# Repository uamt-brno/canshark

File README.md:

canshark
========

Wireshark sniffer for CAN bus

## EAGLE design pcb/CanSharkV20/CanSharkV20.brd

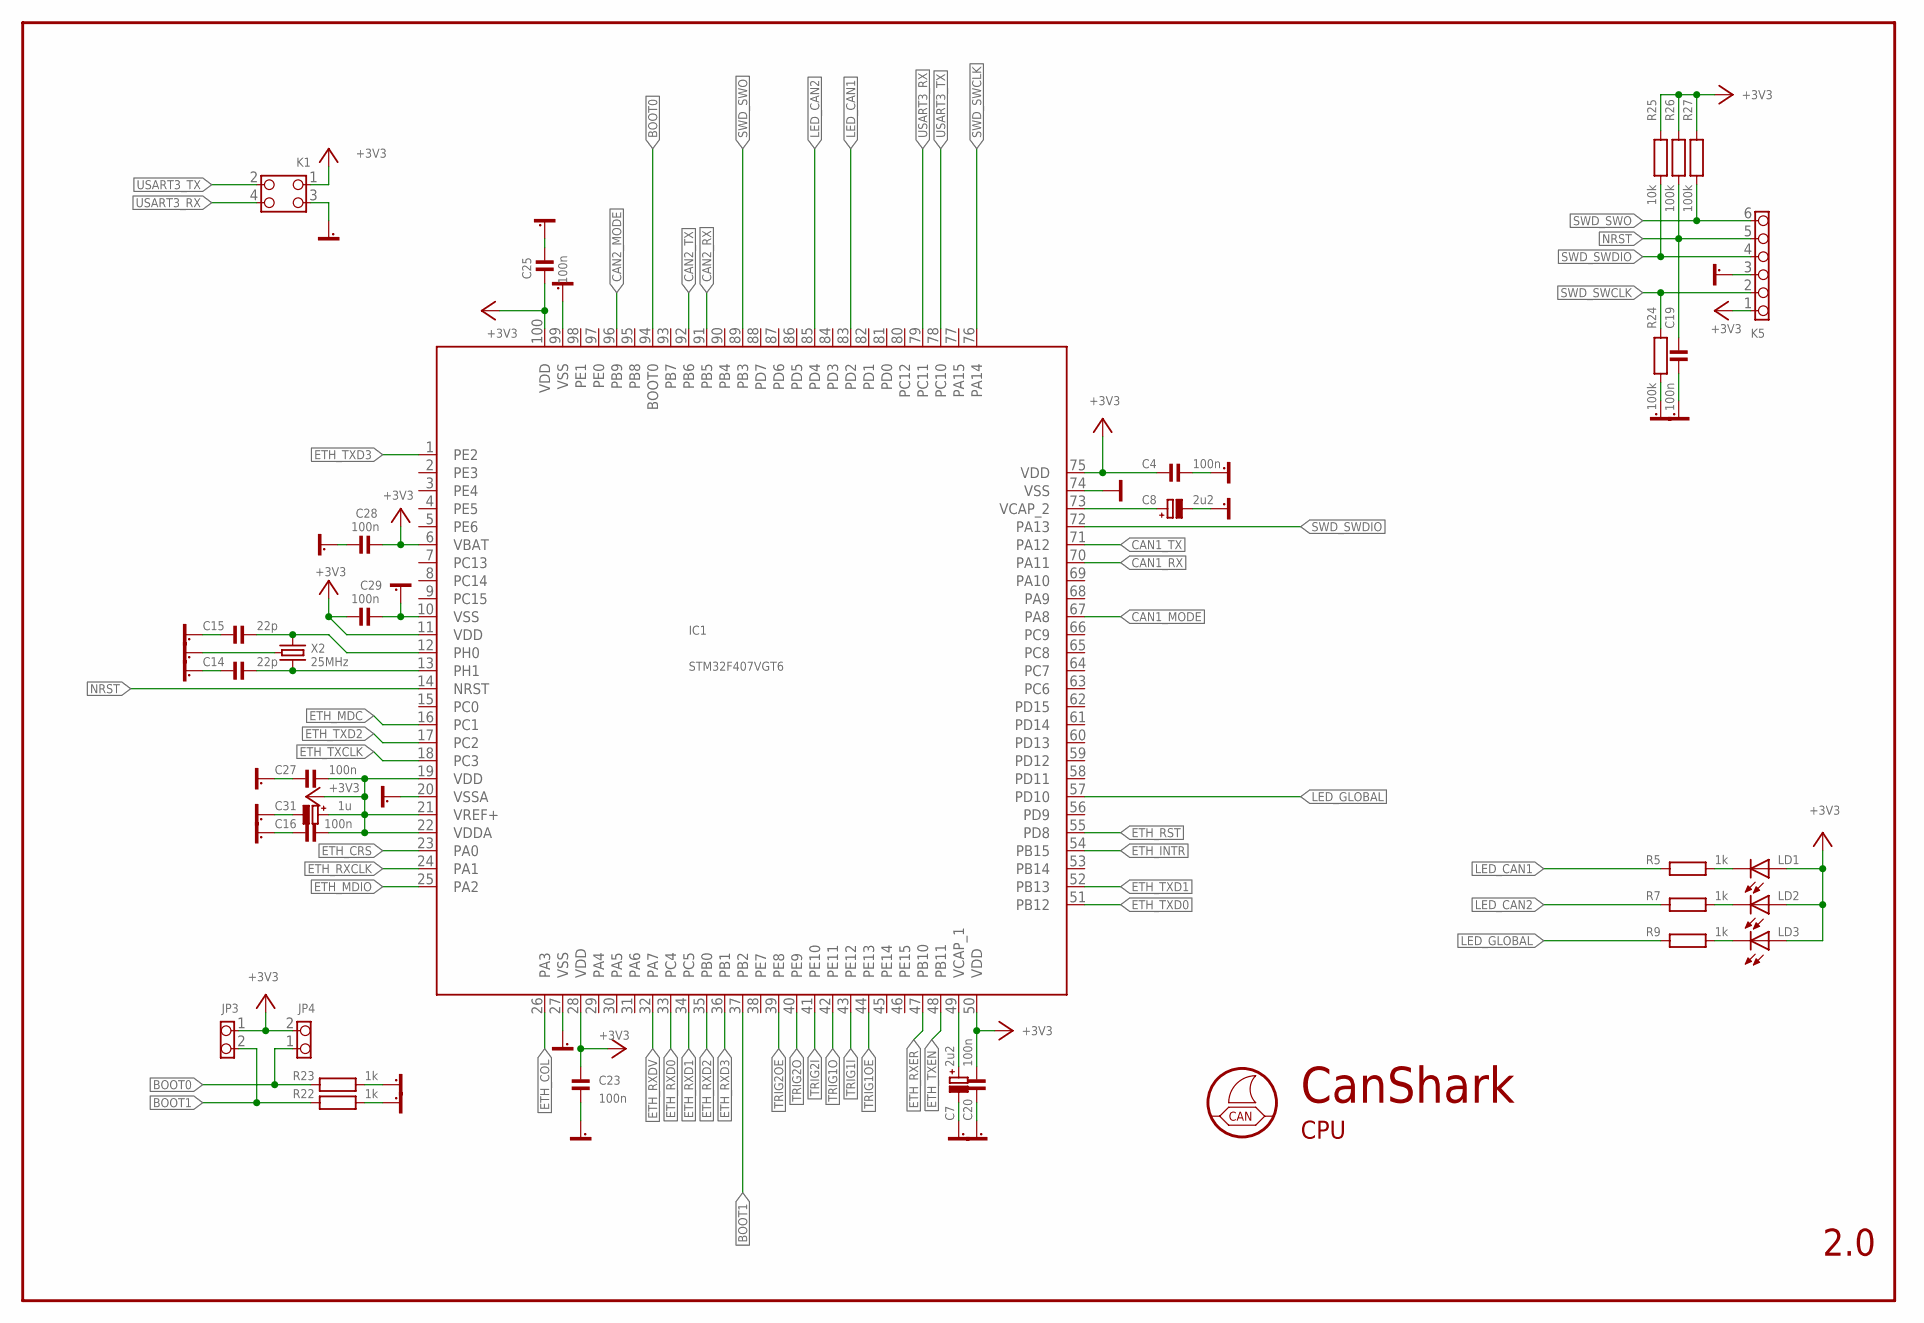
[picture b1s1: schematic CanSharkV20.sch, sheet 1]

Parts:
C4, C16, C19, C20, C23, C25, C27, C28, C29: 100n; 0603
C7, C8: 2u2; CT3216A
C14, C15: 22p; 0603
C31: 1u; CT3216A
IC1: STM32F407VGT6; LQFP100
JP3, JP4: PINHD-1X2; 1X02_254
K1: PINHD-2X2; 2X02_254
K5: PINHD-1X6; 1X06_254
LD1, LD2, LD3: TLLG4400; LED3MM
R5, R7, R9, R22, R23: 1k; 0603
R24, R25, R27: 100k; 0603
R26: 10k; 0603
X2: 25MHz; X_XT324

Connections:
+3V3: C4.2, C16.1, C20.1, C23.1, C25.2, C27.1, C28.2, C29.2, C31.+, IC1.6 (VBAT), IC1.11 (VDD), IC1.19 (VDD), IC1.21 (VREF+), IC1.22 (VDDA), IC1.28 (VDD), IC1.50 (VDD), IC1.75 (VDD), IC1.100 (VDD), JP3.1, JP4.2, K1.1, K5.1, LD1.A, LD2.A, LD3.A, R25.1, R26.2, R27.1; also elsewhere on the board
BOOT0: IC1.94 (BOOT0), JP4.1, R23.2
BOOT1: IC1.37 (PB2), JP3.2, R22.2
CAN1_MODE: IC1.67 (PA8); also elsewhere on the board
CAN1_RX: IC1.70 (PA11); also elsewhere on the board
CAN1_TX: IC1.71 (PA12); also elsewhere on the board
CAN2_MODE: IC1.96 (PB9); also elsewhere on the board
CAN2_RX: IC1.91 (PB5); also elsewhere on the board
CAN2_TX: IC1.92 (PB6); also elsewhere on the board
ETH_COL: IC1.26 (PA3); also elsewhere on the board
ETH_CRS: IC1.23 (PA0); also elsewhere on the board
ETH_INTR: IC1.54 (PB15); also elsewhere on the board
ETH_MDC: IC1.16 (PC1); also elsewhere on the board
ETH_MDIO: IC1.25 (PA2); also elsewhere on the board
ETH_RST: IC1.55 (PD8); also elsewhere on the board
ETH_RXCLK: IC1.24 (PA1); also elsewhere on the board
ETH_RXD0: IC1.33 (PC4); also elsewhere on the board
ETH_RXD1: IC1.34 (PC5); also elsewhere on the board
ETH_RXD2: IC1.35 (PB0); also elsewhere on the board
ETH_RXD3: IC1.36 (PB1); also elsewhere on the board
ETH_RXDV: IC1.32 (PA7); also elsewhere on the board
ETH_RXER: IC1.47 (PB10); also elsewhere on the board
ETH_TXCLK: IC1.18 (PC3); also elsewhere on the board
ETH_TXD0: IC1.51 (PB12); also elsewhere on the board
ETH_TXD1: IC1.52 (PB13); also elsewhere on the board
ETH_TXD2: IC1.17 (PC2); also elsewhere on the board
ETH_TXD3: IC1.1 (PE2); also elsewhere on the board
ETH_TXEN: IC1.48 (PB11); also elsewhere on the board
GND: IC1.74 (VSS)
GND1: C4.1, C7.-, C8.-, C14.2, C15.2, C16.2, C19.2, C20.2, C23.2, C25.1, C27.2, C28.1, C29.1, C31.-, IC1.10 (VSS), IC1.20 (VSSA), IC1.27 (VSS), IC1.99 (VSS), K1.3, K5.3, R22.1, R23.1, R24.2, X2.2 (G), X2.4 (G); also elsewhere on the board
LED_CAN1: IC1.83 (PD2), R5.2
LED_CAN2: IC1.85 (PD4), R7.2
LED_GLOBAL: IC1.57 (PD10), R9.2
unnamed: C7.+, IC1.49 (VCAP_1)
unnamed: C8.+, IC1.73 (VCAP_2)
unnamed: LD1.K (C), R5.1
unnamed: LD2.K (C), R7.1
unnamed: LD3.K (C), R9.1
NRST: C19.1, IC1.14 (NRST), K5.5, R26.1
OSC_IN: C15.1, IC1.12 (PH0), X2.1
OSC_OUT: C14.1, IC1.13 (PH1), X2.3 (2)
SWD_SWCLK: IC1.76 (PA14), K5.2, R24.1
SWD_SWDIO: IC1.72 (PA13), K5.4, R25.2
SWD_SWO: IC1.89 (PB3), K5.6, R27.2
TRIG1I: IC1.43 (PE12); also elsewhere on the board
TRIG1O: IC1.42 (PE11); also elsewhere on the board
TRIG1OE: IC1.44 (PE13); also elsewhere on the board
TRIG2I: IC1.41 (PE10); also elsewhere on the board
TRIG2O: IC1.40 (PE9); also elsewhere on the board
TRIG2OE: IC1.39 (PE8); also elsewhere on the board
USART3_RX: IC1.79 (PC11), K1.4
USART3_TX: IC1.78 (PC10), K1.2

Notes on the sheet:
CAN
2.0
CanShark
CPU

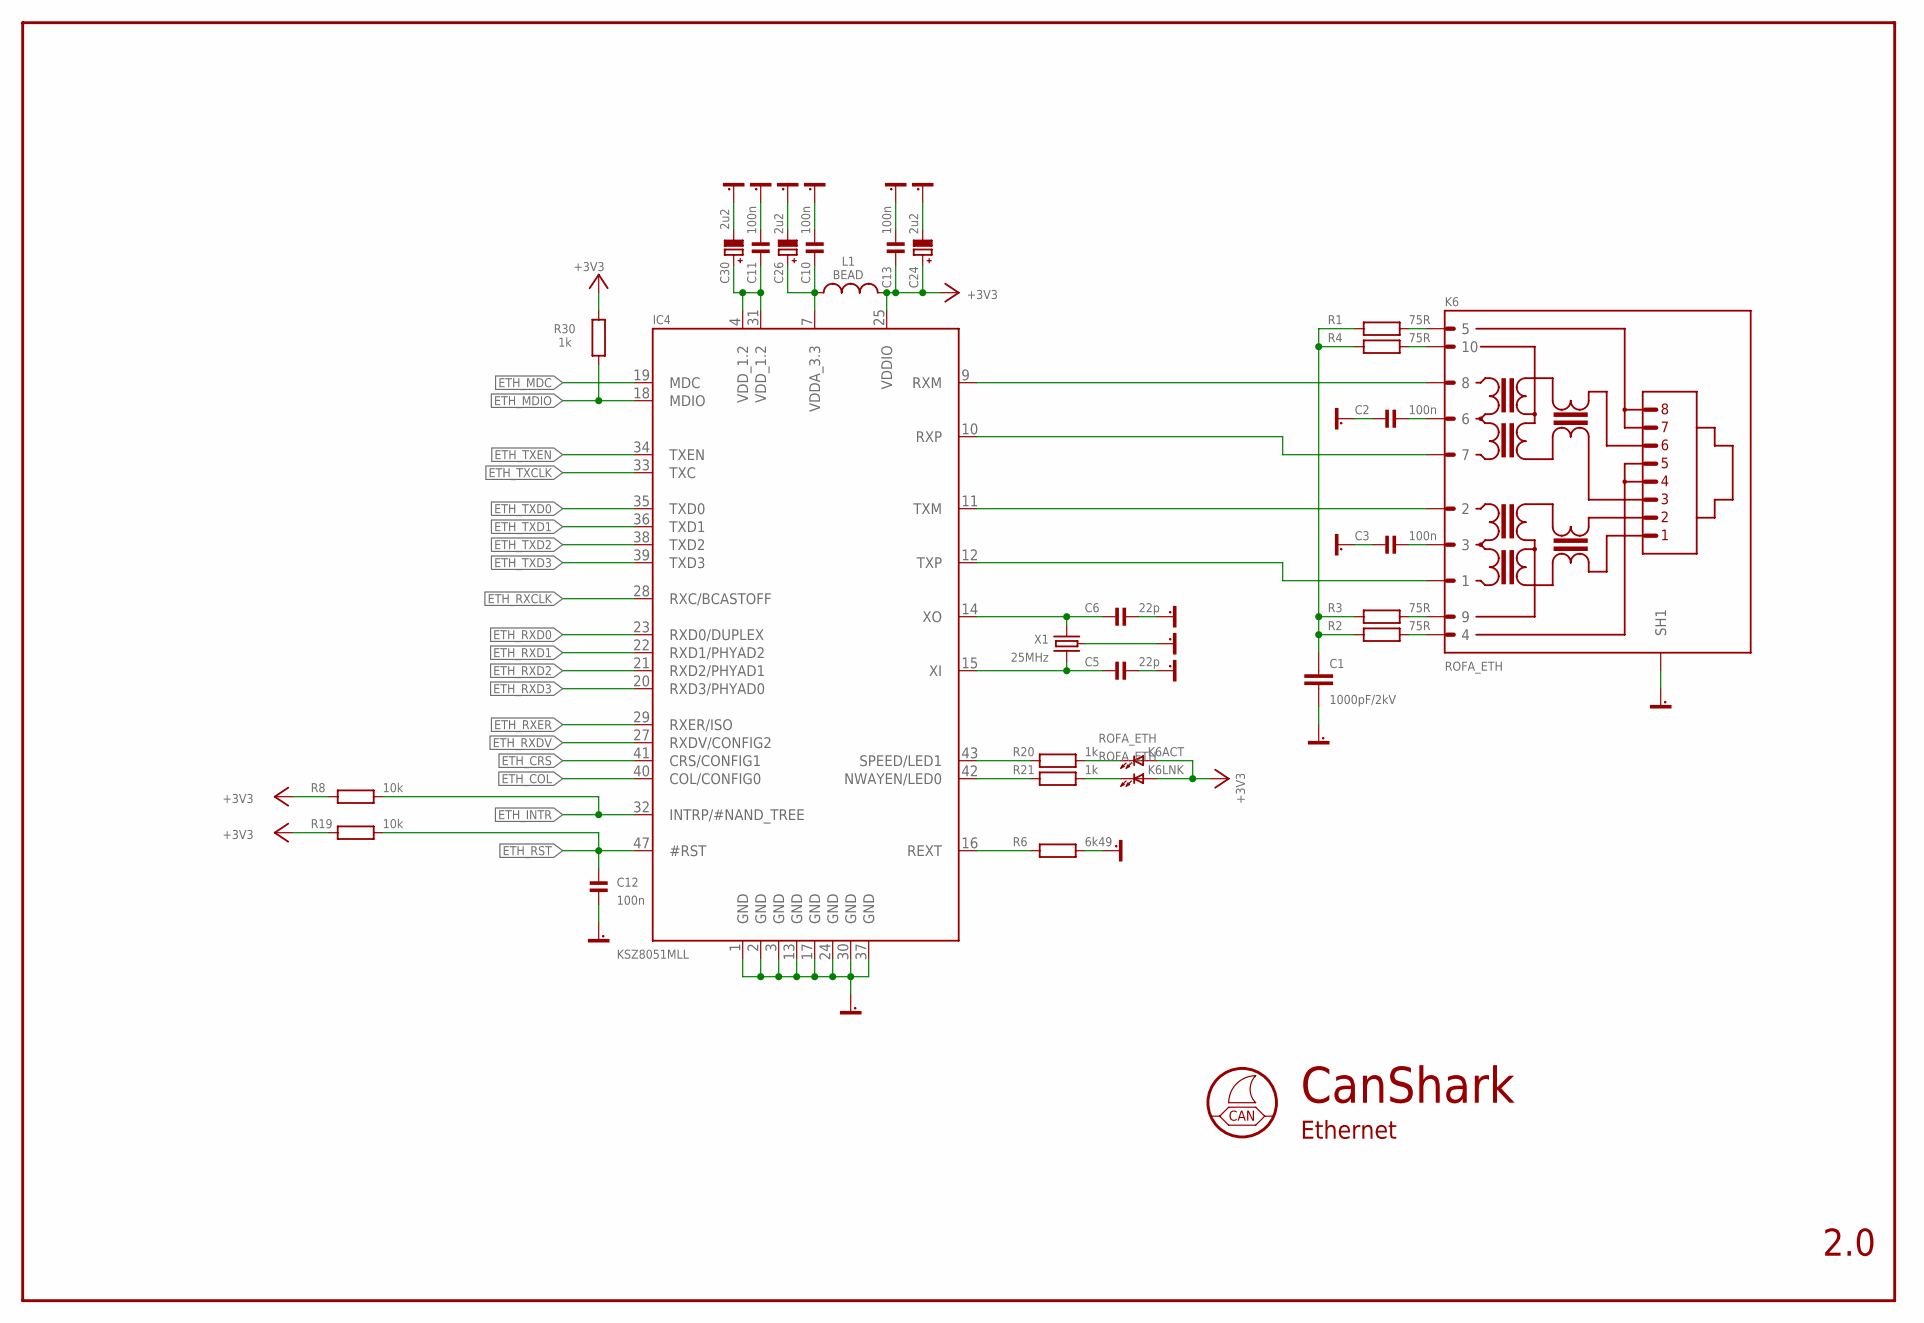
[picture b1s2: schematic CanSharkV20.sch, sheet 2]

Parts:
C1: 1000pF/2kV; SMD1206
C2, C3, C10, C11, C12, C13: 100n; 0603
C5, C6: 22p; 0603
C24, C26, C30: 2u2; CT3216A
IC4: KSZ8051MLL; LQFP48
K6: ROFA_ETH; RJ45_TRAFO
L1: BEAD; 1206
R1, R2, R3, R4: 75R; 0603
R6: 6k49; 0603
R8, R19: 10k; 0603
R20, R21, R30: 1k; 0603
X1: 25MHz; X_XT324

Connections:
+3V3: C13.2, C24.+, IC4.25 (VDDIO), K6.A_G (A), K6.A_Y (A), L1.1, R8.1, R19.1, R30.2; also elsewhere on the board
ETH_COL: IC4.40 (COL/CONFIG0); also elsewhere on the board
ETH_CRS: IC4.41 (CRS/CONFIG1); also elsewhere on the board
ETH_INTR: IC4.32 (INTRP/#NAND_TREE), R8.2; also elsewhere on the board
ETH_MDC: IC4.19 (MDC); also elsewhere on the board
ETH_MDIO: IC4.18 (MDIO), R30.1; also elsewhere on the board
ETH_RST: C12.1, IC4.47 (#RST), R19.2; also elsewhere on the board
ETH_RXCLK: IC4.28 (RXC/BCASTOFF); also elsewhere on the board
ETH_RXD0: IC4.23 (RXD0/DUPLEX); also elsewhere on the board
ETH_RXD1: IC4.22 (RXD1/PHYAD2); also elsewhere on the board
ETH_RXD2: IC4.21 (RXD2/PHYAD1); also elsewhere on the board
ETH_RXD3: IC4.20 (RXD3/PHYAD0); also elsewhere on the board
ETH_RXDV: IC4.27 (RXDV/CONFIG2); also elsewhere on the board
ETH_RXER: IC4.29 (RXER/ISO); also elsewhere on the board
ETH_TXCLK: IC4.33 (TXC); also elsewhere on the board
ETH_TXD0: IC4.35 (TXD0); also elsewhere on the board
ETH_TXD1: IC4.36 (TXD1); also elsewhere on the board
ETH_TXD2: IC4.38 (TXD2); also elsewhere on the board
ETH_TXD3: IC4.39 (TXD3); also elsewhere on the board
ETH_TXEN: IC4.34 (TXEN); also elsewhere on the board
GND1: C1.2, C2.1, C3.1, C5.1, C6.1, C10.1, C11.1, C12.2, C13.1, C24.-, C26.-, C30.-, IC4.1 (GND), IC4.2 (GND), IC4.3 (GND), IC4.13 (GND), IC4.17 (GND), IC4.24 (GND), IC4.30 (GND), IC4.37 (GND), K6.SH1, K6.SH2 (SH1), R6.1, X1.2 (G), X1.4 (G); also elsewhere on the board
unnamed: K6.K_Y (K), R20.2
unnamed: K6.K_G (K), R21.2
unnamed: C10.2, C26.+, IC4.7 (VDDA_3.3), L1.2
unnamed: C11.2, C30.+, IC4.4 (VDD_1.2), IC4.31 (VDD_1.2)
unnamed: IC4.9 (RXM), K6.8
unnamed: IC4.10 (RXP), K6.7
unnamed: IC4.11 (TXM), K6.2
unnamed: IC4.12 (TXP), K6.1
unnamed: K6.4, R2.2
unnamed: K6.9, R3.2
unnamed: K6.10, R4.2
unnamed: K6.5, R1.2
unnamed: C1.1, R1.1, R2.1, R3.1, R4.1
unnamed: C2.2, K6.6
unnamed: C3.2, K6.3
unnamed: IC4.16 (REXT), R6.2
unnamed: IC4.42 (NWAYEN/LED0), R21.1
unnamed: IC4.43 (SPEED/LED1), R20.1
unnamed: C6.2, IC4.14 (XO), X1.3 (2)
unnamed: C5.2, IC4.15 (XI), X1.1

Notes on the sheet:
CAN
2.0
CanShark
Ethernet

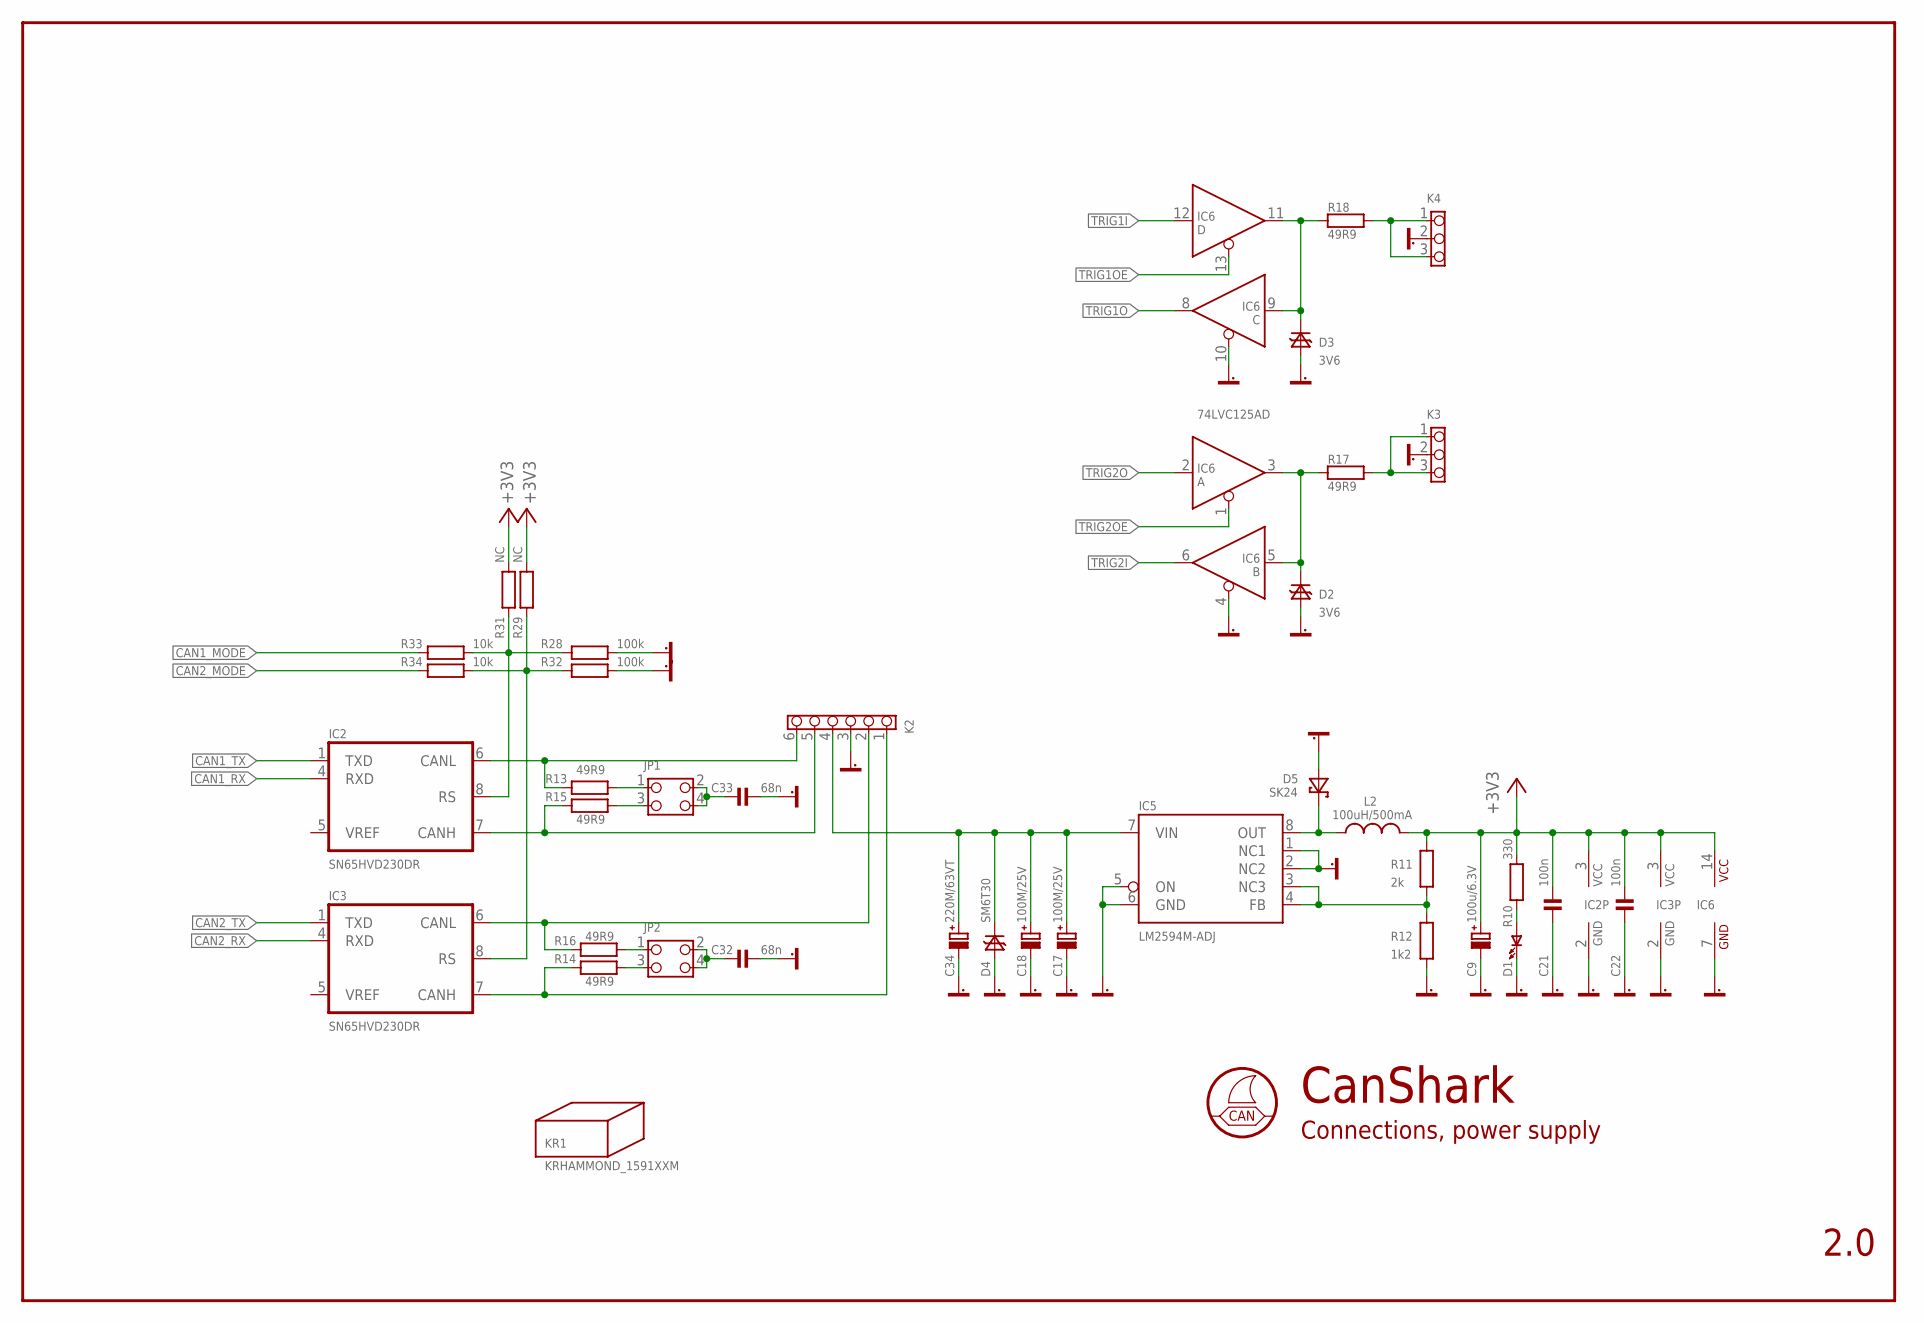
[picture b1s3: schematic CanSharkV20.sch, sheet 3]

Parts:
C9: 100u/6.3V; CT3528B
C17, C18: 100M/25V; CT7343D
C21, C22: 100n; 0603
C32, C33: 68n; 0805
C34: 220M/63VT; CE_D10L13_R
D1: LED0805; LED_0805
D2, D3: 3V6; D_SMA
D4: SM6T30; D_SMB
D5: SK24; D_SMB
IC2, IC3: SN65HVD230DR; SO08
IC5: LM2594M-ADJ; SO08
IC6: 74LVC125AD; SO14
JP1, JP2: PINHD-2X2_254_EDGE; 2X02_254_EDGE
K2: PINHD-1X6_381_V; 1X06_381_V
K3, K4: PINHD-1X3; 1X03_254
KR1: KRHAMMOND_1591XXM; HAMMOND_1591XXM
L2: 100uH/500mA; L_MLC12XX
R10: 330; 0603
R11: 2k; 0603
R12: 1k2; 0603
R13, R14, R15, R16, R17, R18: 49R9; 0805
R28, R32: 100k; 0603
R29, R31: NC; 0603
R33, R34: 10k; 0603

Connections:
+3V3: C9.+, C21.1, C22.1, IC2.3 (VCC), IC3.3 (VCC), IC6.14 (VCC), L2.2 (1), R10.1, R11.1, R29.1, R31.1; also elsewhere on the board
CAN1_H: IC2.7 (CANH), K2.5, R15.2
CAN1_L: IC2.6 (CANL), K2.6, R13.2
CAN1_MODE: R33.1; also elsewhere on the board
CAN1_RX: IC2.4 (RXD); also elsewhere on the board
CAN1_TX: IC2.1 (TXD); also elsewhere on the board
CAN2_H: IC3.7 (CANH), K2.1, R14.2
CAN2_L: IC3.6 (CANL), K2.2, R16.2
CAN2_MODE: R34.1; also elsewhere on the board
CAN2_RX: IC3.4 (RXD); also elsewhere on the board
CAN2_TX: IC3.1 (TXD); also elsewhere on the board
EXTSUPPLY: C17.+, C18.+, C34.P (+), D4.K, IC5.7 (VIN), K2.4
GND1: C9.-, C17.-, C18.-, C21.2, C22.2, C32.1, C33.1, C34.M (-), D1.K (C), D2.A, D3.A, D4.A, D5.A, IC2.2 (GND), IC3.2 (GND), IC5.1 (NC1), IC5.2 (NC2), IC5.5 (ON), IC5.6 (GND), IC6.4 (OE), IC6.7 (GND), IC6.10 (OE), K2.3, K3.2, K4.2, R12.2, R28.2, R32.2; also elsewhere on the board
unnamed: D2.K, IC6.3 (Y), IC6.5 (A), R17.1
unnamed: JP2.1, R16.1
unnamed: D1.A, R10.2
unnamed: JP2.3, R14.1
unnamed: C32.2, JP2.2, JP2.4
unnamed: IC2.8 (RS), R28.1, R31.2, R33.2
unnamed: JP1.1, R13.1
unnamed: IC3.8 (RS), R29.2, R32.1, R34.2
unnamed: JP1.3, R15.1
unnamed: C33.2, JP1.2, JP1.4
unnamed: K4.1, K4.3, R18.2
unnamed: K3.1, K3.3, R17.2
unnamed: D5.K, IC5.8 (OUT), L2.1 (2)
unnamed: IC5.3 (NC3), IC5.4 (FB), R11.2, R12.1
unnamed: D3.K, IC6.9 (A), IC6.11 (Y), R18.1
TRIG1I: IC6.12 (A); also elsewhere on the board
TRIG1O: IC6.8 (Y); also elsewhere on the board
TRIG1OE: IC6.13 (OE); also elsewhere on the board
TRIG2I: IC6.6 (Y); also elsewhere on the board
TRIG2O: IC6.2 (A); also elsewhere on the board
TRIG2OE: IC6.1 (OE); also elsewhere on the board

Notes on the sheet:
CAN
2.0
CanShark
Connections, power supply

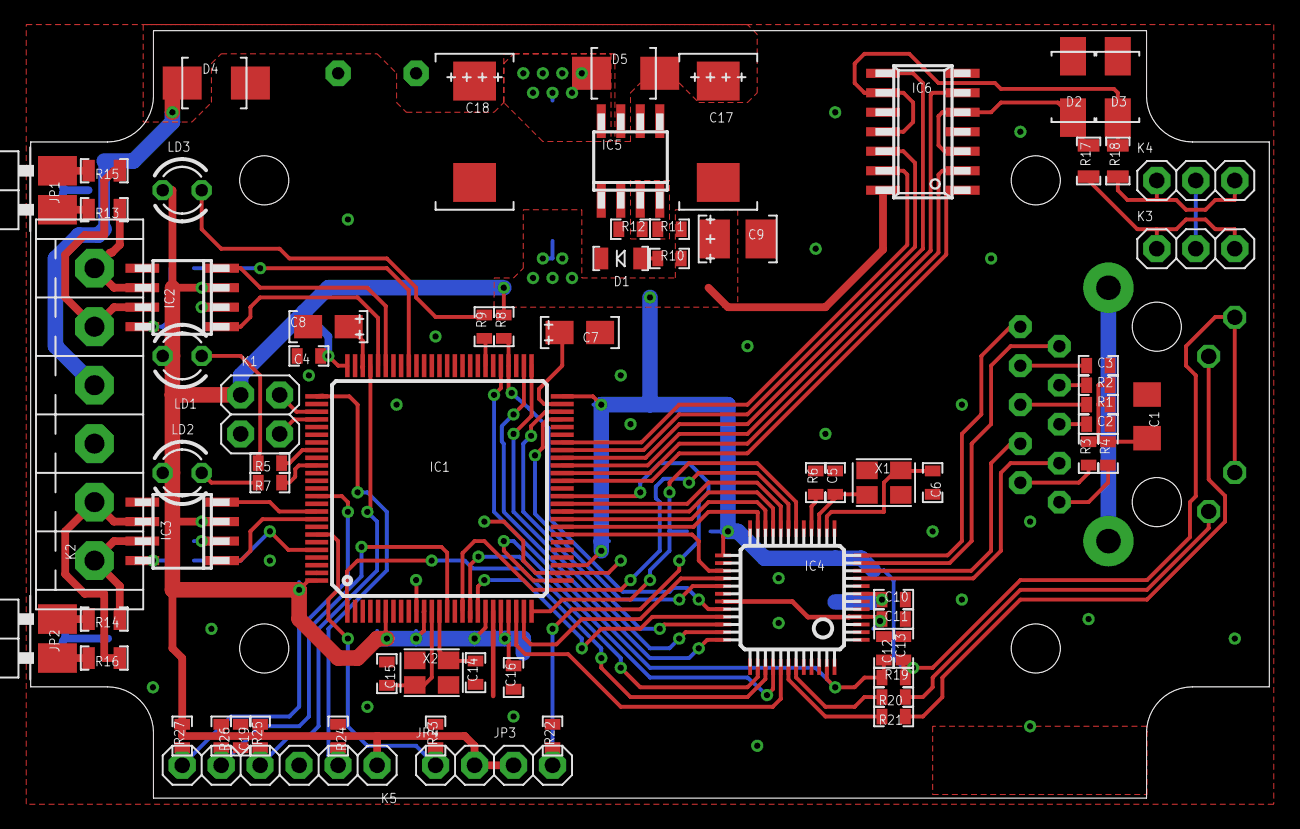
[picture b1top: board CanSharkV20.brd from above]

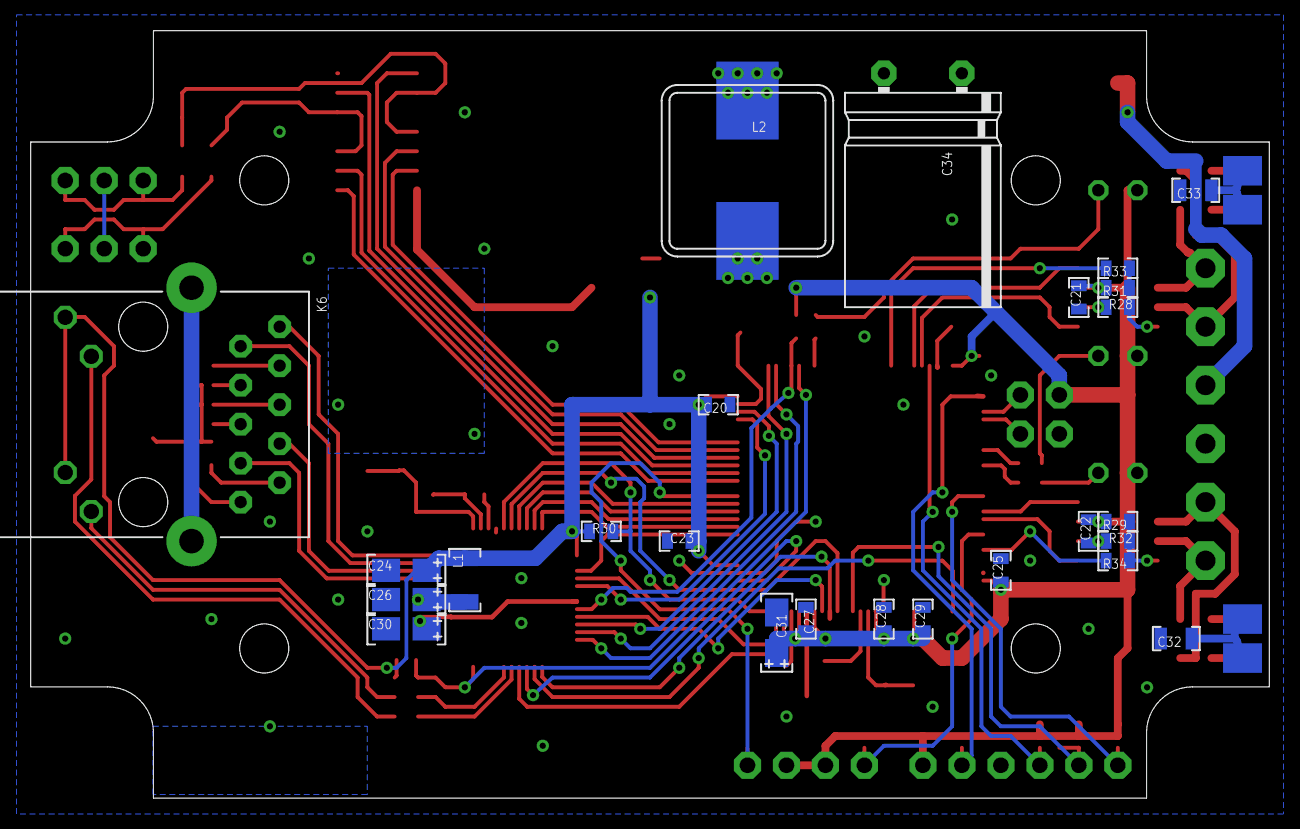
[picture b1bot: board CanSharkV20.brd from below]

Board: 2 copper layers, 80.7 x 50.0 mm, 97 parts (25 on the bottom side), 91 nets.

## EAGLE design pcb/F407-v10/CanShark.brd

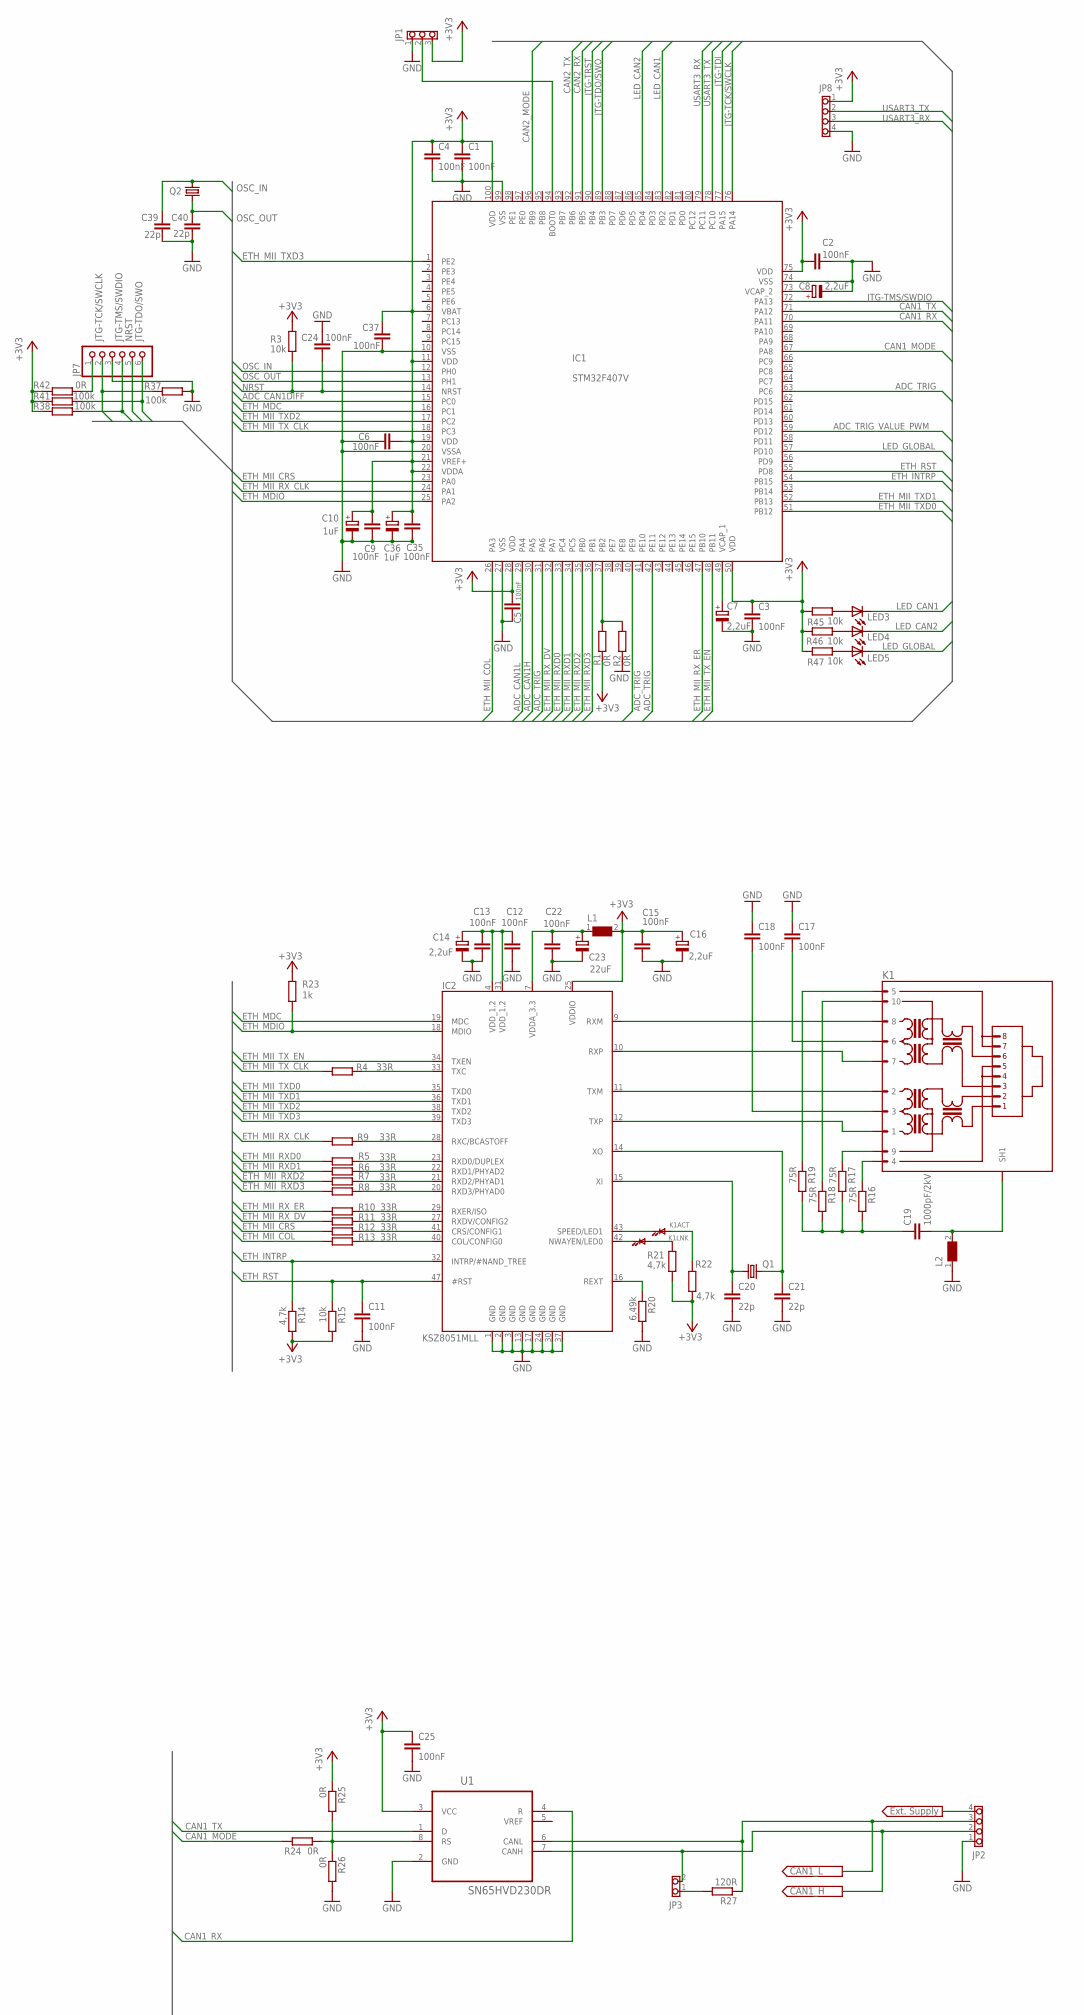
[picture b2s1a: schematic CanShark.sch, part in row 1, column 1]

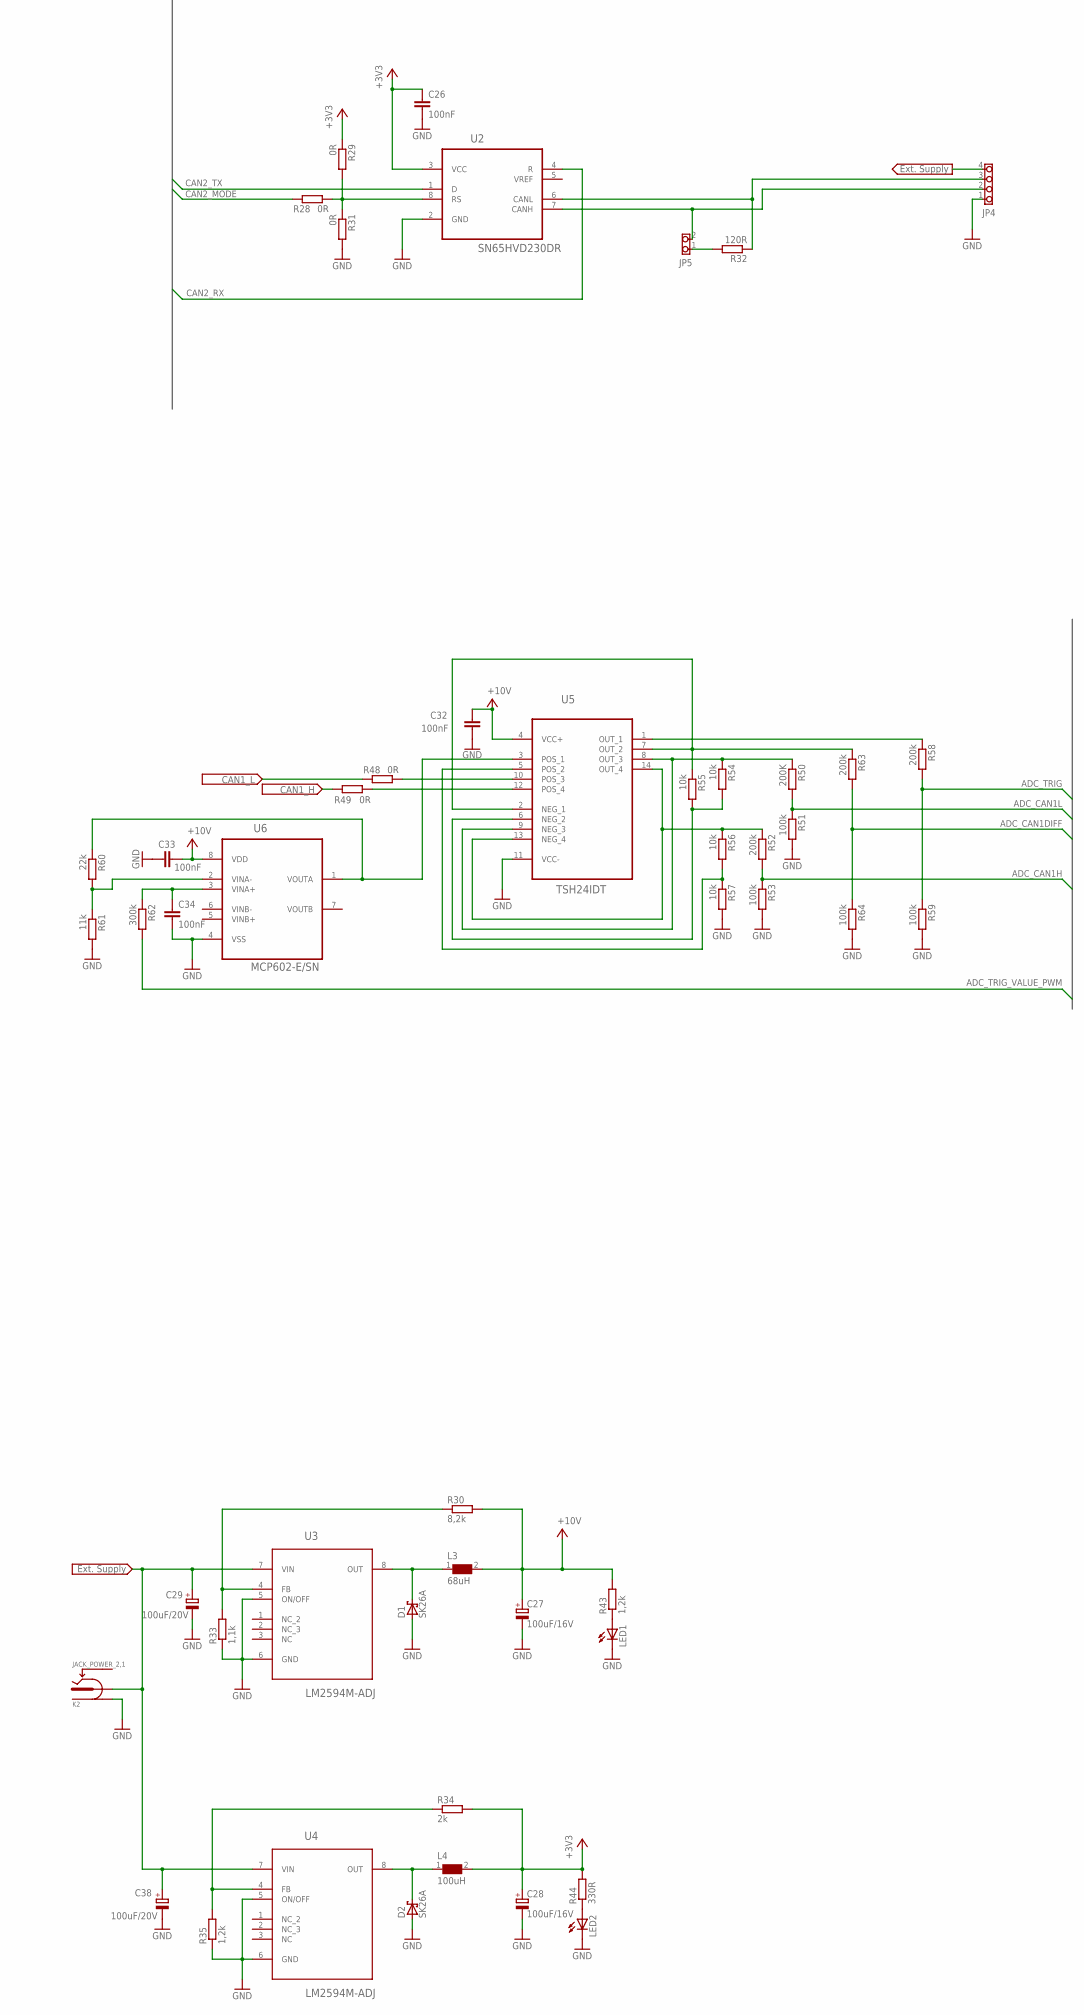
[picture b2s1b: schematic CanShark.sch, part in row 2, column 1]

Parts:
C1, C2, C3, C4, C5, C6, C9, C11, C12, C13, C15, C17, C18, C22, C24, C25, C26, C32, C33, C34, C35, C37: 100nF; SMD0603
C7, C8, C14, C16: 2,2uF; SMC_A
C10, C36: 1uF; SMC_A
C19: 1000pF/2kV; SMD1206
C20, C21, C39, C40: 22p; SMD0603
C23: 22uF; SMC_A
C27, C28: 100uF/16V; C/6032-28R
C29, C38: 100uF/20V; C/6032-28R
D1, D2: SK26A; SMB
IC1: STM32F407V; LQFP100
IC2: KSZ8051MLL; LQFP48
JP1: PINHD-1X3; 1X03_254
JP2, JP4: PINHD-1X4_508_H; 1X04_508_H
JP3, JP5: PINHD-1X2; 1X02_254
JP7: PINHD-1X6; 1X06
JP8: PINHD-1X4; 1X04_254
K1: RJ45_TRAFO
K2: JACK_POWER_2,1; J_P_2,1
L1, L2: WE-CBF_HF-742863122_0603; 0603
L3: 68uH; WE-TPC_1028/1038
L4: 100uH; WE-TPC_1028/1038
LED1, LED2: LEDSML0603; SML0603
LED3, LED4, LED5: TLLG4400; LED3MM
Q1, Q2: CRYSTALHC49U-V; HC49U-V
R1, R2, R24, R25, R26, R28, R29, R31, R42, R48, R49: 0R; R0603
R3, R15, R45, R46, R47, R54, R55, R56, R57: 10k; R0603
R4, R5, R6, R7, R8, R9, R10, R11, R12, R13: 33R; R0603
R14, R21, R22: 4,7k; R0603
R16, R17, R18, R19: 75R; R0603
R20: 6,49k; R0603
R23: 1k; R0603
R27, R32: 120R; R0603
R30: 8,2k; R0603
R33: 1,1k; R0603
R34: 2k; R0603
R35, R43: 1,2k; R0603
R37, R38, R41, R51, R53, R59, R64: 100k; R0603
R44: 330R; R0603
R50: 200K; R0603
R52, R58, R63: 200k; R0603
R60: 22k; R0603
R61: 11k; R0603
R62: 300k; R0603
U1, U2: SN65HVD230DR; SOIC127P600X175-8N
U3, U4: LM2594M-ADJ; SOIC127P620X175-8N
U5: TSH24IDT; SOIC127P600X175-14N
U6: MCP602-E/SN; SOIC127P600X175-8N

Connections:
+3V3: C1.1, C2.1, C3.1, C4.1, C5.1, C6.2, C9.2, C10.+, C15.1, C16.+, C25.1, C26.1, C28.+, C35.2, C36.+, C37.2, IC1.6 (VBAT), IC1.11 (VDD), IC1.19 (VDD), IC1.21 (VREF+), IC1.22 (VDDA), IC1.28 (VDD), IC1.50 (VDD), IC1.75 (VDD), IC1.100 (VDD), IC2.25 (VDDIO), JP1.3, JP8.1, L1.2, L4.2, R1.1, R3.2, R14.2, R15.2, R21.1, R22.1, R23.1, R25.1, R29.1, R34.2, R38.1, R41.1, R42.1, R44.2, R45.2, R46.2, R47.2, U1.3 (VCC), U2.3 (VCC)
ADC_CAN1DIFF: IC1.15 (PC0), R63.2, R64.1
ADC_CAN1H: IC1.30 (PA5), R52.2, R53.1
ADC_CAN1L: IC1.29 (PA4), R50.2, R51.1
ADC_TRIG: IC1.31 (PA6), IC1.40 (PE9), IC1.42 (PE11), IC1.63 (PC6), R58.2, R59.1
ADC_TRIG_VALUE_PWM: IC1.59 (PD12), R62.2
CAN1_H: JP2.2, JP3.2, R49.2, U1.7 (CANH)
CAN1_L: JP2.3, R27.1, R48.2, U1.6 (CANL)
CAN1_MODE: IC1.67 (PA8), R24.1
CAN1_RX: IC1.70 (PA11), U1.4 (R)
CAN1_TX: IC1.71 (PA12), U1.1 (D)
CAN2_MODE: IC1.96 (PB9), R28.1
CAN2_RX: IC1.91 (PB5), U2.4 (R)
CAN2_TX: IC1.92 (PB6), U2.1 (D)
CANL: JP4.3, R32.1, U2.6 (CANL)
ETH_INTRP: IC1.54 (PB15), IC2.32 (INTRP/#NAND_TREE), R14.1
ETH_MDC: IC1.16 (PC1), IC2.19 (MDC)
ETH_MDIO: IC1.25 (PA2), IC2.18 (MDIO), R23.2
ETH_MII_COL: IC1.26 (PA3), R13.2
ETH_MII_CRS: IC1.23 (PA0), R12.2
ETH_MII_RXD0: IC1.33 (PC4), R5.2
ETH_MII_RXD1: IC1.34 (PC5), R6.2
ETH_MII_RXD2: IC1.35 (PB0), R7.2
ETH_MII_RXD3: IC1.36 (PB1), R8.2
ETH_MII_RX_CLK: IC1.24 (PA1), R9.2
ETH_MII_RX_DV: IC1.32 (PA7), R11.2
ETH_MII_RX_ER: IC1.47 (PB10), R10.2
ETH_MII_TXD0: IC1.51 (PB12), IC2.35 (TXD0)
ETH_MII_TXD1: IC1.52 (PB13), IC2.36 (TXD1)
ETH_MII_TXD2: IC1.17 (PC2), IC2.38 (TXD2)
ETH_MII_TXD3: IC1.1 (PE2), IC2.39 (TXD3)
ETH_MII_TX_CLK: IC1.18 (PC3), R4.2
ETH_MII_TX_EN: IC1.48 (PB11), IC2.34 (TXEN)
ETH_RST: C11.1, IC1.55 (PD8), IC2.47 (#RST), R15.1
EXTSUPPLY: C29.+, C38.+, JP2.4, JP4.4, K2.A, U3.7 (VIN), U4.7 (VIN)
GND: C1.2, C2.2, C3.2, C4.2, C5.2, C6.1, C7.-, C8.-, C9.1, C10.-, C11.2, C12.2, C13.2, C14.-, C15.2, C16.-, C17.1, C18.1, C20.2, C21.2, C22.2, C23.-, C24.2, C25.2, C26.2, C27.-, C28.-, C29.-, C32.2, C33.2, C34.2, C35.1, C36.-, C37.1, C38.-, C39.2, C40.2, D1.A, D2.A, IC1.10 (VSS), IC1.20 (VSSA), IC1.27 (VSS), IC1.74 (VSS), IC1.99 (VSS), IC2.1 (GND), IC2.2 (GND), IC2.3 (GND), IC2.13 (GND), IC2.17 (GND), IC2.24 (GND), IC2.30 (GND), IC2.37 (GND), JP1.1, JP2.1, JP4.1, JP7.3, JP8.4, K2.B, L2.1, LED1.C, LED2.C, R2.1, R20.2, R26.2, R31.2, R33.1, R35.1, R37.2, R51.2, R53.2, R57.2, R59.2, R61.2, R64.2, U1.2 (GND), U2.2 (GND), U3.5 (ON/OFF), U3.6 (GND), U4.5 (ON/OFF), U4.6 (GND), U5.11 (VCC-), U6.4 (VSS)
JTG-TCK/SWCLK: IC1.76 (PA14), JP7.2, R37.1
JTG-TDI: IC1.77 (PA15)
JTG-TDO/SWO: IC1.89 (PB3), JP7.6, R41.2
JTG-TMS/SWDIO: IC1.72 (PA13), JP7.4, R38.2
JTG-TRST: IC1.90 (PB4)
LED_CAN1: IC1.83 (PD2), LED3.K (C)
LED_CAN2: IC1.85 (PD4), LED4.K (C)
LED_GLOBAL: IC1.57 (PD10), LED5.K (C)
unnamed: IC1.94 (BOOT0), JP1.2
unnamed: C7.+, IC1.49 (VCAP_1)
unnamed: C8.+, IC1.73 (VCAP_2)
unnamed: JP3.1, R27.2
unnamed: IC1.37 (PB2), R1.2, R2.2
unnamed: D1.C, L3.1, U3.8 (OUT)
unnamed: C22.1, C23.+, IC2.7 (VDDA_3.3), L1.1
unnamed: IC2.33 (TXC), R4.1
unnamed: R24.2, R25.2, R26.1, U1.8 (RS)
unnamed: JP4.2, JP5.2, U2.7 (CANH)
unnamed: IC2.28 (RXC/BCASTOFF), R9.1
unnamed: R28.2, R29.2, R31.1, U2.8 (RS)
unnamed: IC2.23 (RXD0/DUPLEX), R5.1
unnamed: IC2.22 (RXD1/PHYAD2), R6.1
unnamed: IC2.21 (RXD2/PHYAD1), R7.1
unnamed: IC2.20 (RXD3/PHYAD0), R8.1
unnamed: IC2.29 (RXER/ISO), R10.1
unnamed: IC2.27 (RXDV/CONFIG2), R11.1
unnamed: IC2.41 (CRS/CONFIG1), R12.1
unnamed: IC2.40 (COL/CONFIG0), R13.1
unnamed: JP5.1, R32.2
unnamed: JP7.1, R42.2
unnamed: D2.C, L4.1, U4.8 (OUT)
unnamed: R34.1, R35.2, U4.4 (FB)
unnamed: R30.1, R33.2, U3.4 (FB)
unnamed: LED1.A, R43.1
unnamed: C12.1, C13.1, C14.+, IC2.4 (VDD_1.2), IC2.31 (VDD_1.2)
unnamed: IC2.9 (RXM), K1.8
unnamed: IC2.10 (RXP), K1.7
unnamed: IC2.11 (TXM), K1.2
unnamed: IC2.12 (TXP), K1.1
unnamed: K1.4, R16.1
unnamed: K1.9, R17.1
unnamed: K1.10, R18.1
unnamed: K1.5, R19.1
unnamed: C19.1, R16.2, R17.2, R18.2, R19.2
unnamed: C17.2, K1.6
unnamed: C18.2, K1.3
unnamed: C19.2, K1.SH1, K1.SH2 (SH1), L2.2
unnamed: IC2.16 (REXT), R20.1
unnamed: IC2.42 (NWAYEN/LED0), K1.K_G (K)
unnamed: IC2.43 (SPEED/LED1), K1.K_Y (K)
unnamed: K1.A_Y (A), R22.2
unnamed: K1.A_G (A), R21.2
unnamed: LED2.A, R44.1
unnamed: C21.1, IC2.14 (XO), Q1.2
unnamed: C20.1, IC2.15 (XI), Q1.1
unnamed: LED3.A, R45.1
unnamed: LED4.A, R46.1
unnamed: LED5.A, R47.1
unnamed: R52.1, R56.1, U5.13 (NEG_4), U5.14 (OUT_4)
unnamed: R50.1, R54.1, U5.8 (OUT_3), U5.9 (NEG_3)
unnamed: R49.1, U5.12 (POS_4)
unnamed: R48.1, U5.10 (POS_3)
unnamed: R55.1, R63.1, U5.2 (NEG_1), U5.7 (OUT_2)
unnamed: R54.2, R55.2, U5.6 (NEG_2)
unnamed: R56.2, R57.1, U5.5 (POS_2)
unnamed: R60.1, U5.3 (POS_1), U6.1 (VOUTA)
unnamed: R58.1, U5.1 (OUT_1)
unnamed: R60.2, R61.1, U6.2 (VINA-)
unnamed: C34.1, R62.1, U6.3 (VINA+)
NRST: C24.1, IC1.14 (NRST), JP7.5, R3.1
OSC_IN: C39.1, IC1.12 (PH0), Q2.2
OSC_OUT: C40.1, IC1.13 (PH1), Q2.1
USART3_RX: IC1.79 (PC11), JP8.3
USART3_TX: IC1.78 (PC10), JP8.2
V+: C27.+, C32.1, C33.1, L3.2, R30.2, R43.2, U5.4 (VCC+), U6.8 (VDD)

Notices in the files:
parts and their libraries:
Copyright (C) Vlada 2004-2005
